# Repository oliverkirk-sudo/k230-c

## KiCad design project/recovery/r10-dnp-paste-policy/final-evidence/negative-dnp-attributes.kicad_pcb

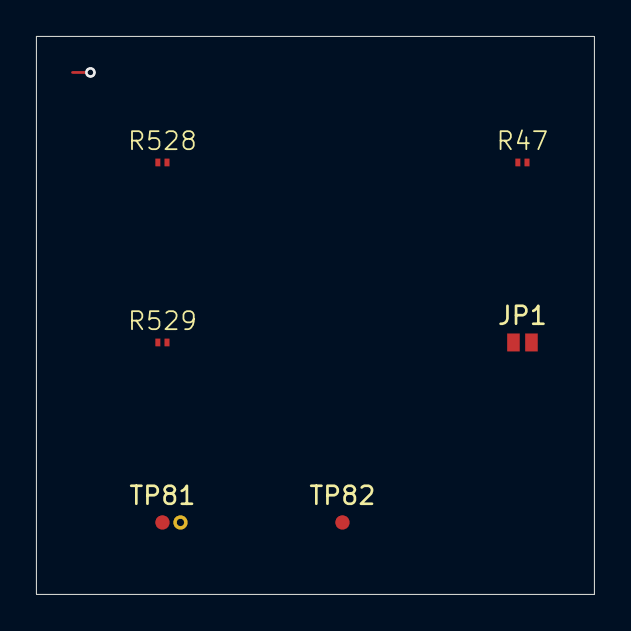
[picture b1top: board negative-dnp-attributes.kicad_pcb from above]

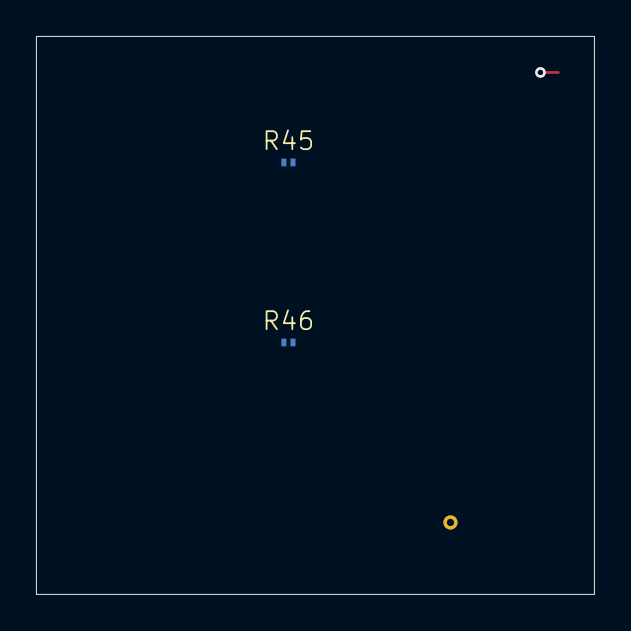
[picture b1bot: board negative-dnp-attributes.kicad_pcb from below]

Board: 2 copper layers, 31.0 x 31.0 mm, 8 parts (2 on the bottom side), 4 nets.

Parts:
JP1: OPEN=EMMC / CLOSED=TF; COLD ONLY; Core_Cold_Selector_Open_SolderBridge_CANDIDATE
R45: 10k BOOT0 HIGH / DNP; Vishay_CRCW0201_SourceLand_PROCESS_CANDIDATE
R46: 10k BOOT1 HIGH; Vishay_CRCW0201_SourceLand_PROCESS_CANDIDATE
R47: 10k BOOT1 LOW / DNP; Vishay_CRCW0201_SourceLand_PROCESS_CANDIDATE
R528: 0R QUALIFICATION STRAP DNP; Vishay_CRCW0201_SourceLand_PROCESS_CANDIDATE
R529: 100k DEFAULT INHIBIT; Vishay_CRCW0201_SourceLand_PROCESS_CANDIDATE
TP81: PMU OUT0 OBSERVE ONLY; Core_PMUSTATUS_Top_TestPad_0p8_CANDIDATE
TP82: PMU OUT1 OBSERVE ONLY; Core_PMUSTATUS_Top_TestPad_0p8_CANDIDATE

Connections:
BOOT1: R46.1, R47.1
BOOT_VOLTAGE_QUALIFIED_1V8: R528.2, R529.1
GND: R47.2, R529.2
VDD1P8: R45.2, R46.2, R528.1

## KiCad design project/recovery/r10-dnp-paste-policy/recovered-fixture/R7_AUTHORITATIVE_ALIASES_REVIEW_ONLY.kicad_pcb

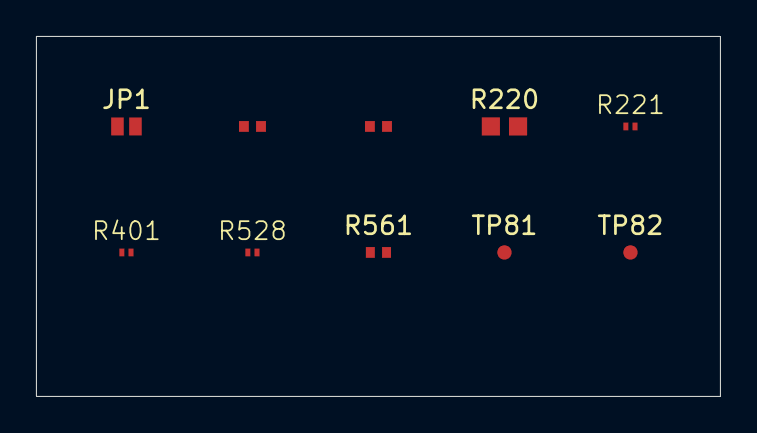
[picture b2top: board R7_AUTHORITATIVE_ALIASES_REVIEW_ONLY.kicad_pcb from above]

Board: 6 copper layers, 38.0 x 20.0 mm, 10 parts (0 on the bottom side), 3 nets, no tracks yet.

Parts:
JP1: OPEN=EMMC / CLOSED=TF; COLD ONLY; Core_Cold_Selector_Open_SolderBridge_CANDIDATE
R205, R206: 56.2k 1% / 0.8V / addr0x49; Vishay_TNPW0402_IPC7351_SourceLand_PROCESS_CANDIDATE
R220: 0R WSL060300000ZEA9 Rmax=0.25mOhm; Vishay_WSL0603_9_SourceLand_PROCESS_CANDIDATE
R221: 0R Rmax<=50mOhm; Vishay_CRCW0201_SourceLand_PROCESS_CANDIDATE
R401: 0R PMU AUTO-START STRAP; Vishay_CRCW0201_SourceLand_PROCESS_CANDIDATE
R528: 0R QUALIFICATION STRAP DNP; Vishay_CRCW0201_SourceLand_PROCESS_CANDIDATE
R561: 0R WFZ040200000ZE66 3mOhm CANDIDATE; Vishay_WFZ0402_SourceLand_PROCESS_CANDIDATE
TP81: PMU OUT0 OBSERVE ONLY; Core_PMUSTATUS_Top_TestPad_0p8_CANDIDATE
TP82: PMU OUT1 OBSERVE ONLY; Core_PMUSTATUS_Top_TestPad_0p8_CANDIDATE

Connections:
GND: R205.2, R206.2
VDD1P8: R528.1, R561.1
VDD_3V3: JP1.2, R221.1
